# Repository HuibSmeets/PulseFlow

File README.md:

# PulseFlow
Control the speed of a cooling fan with your heart rate while riding/using your indoor trainer.

Image: Prototype, work in progress

## Description

**PulseFlow** is a small Arduino sketch that connects via BLE to a HR fitness sensor like those from Garmin, Wahoo and others. The fan is connected to a PWM controllable AC dimmer or a dimmer that exposes 2 pins: Output Zerocross detection, input triac trigger. These AC dimmers can be sourced from marketplaces like AliExpress.

## Warning
BE AWARE THAT YOU'LL BE WORKING WITH DEADLY LIVE VOLTAGES. TAKE APPROPRIATE SAFETY MEASURES WHEN CONNECTING PARTS AND WHILE USING THE DEVICE YOU CREATED. 

## Limitations

+ Your HR sensor must allow for multiple BLE connections as your trainer software/device will possiby have to connect to the sensor too using BLE (Garmin HR-Dual sensor supports multiple BLE connections)
+ Sensor pairing is hardcoded, see the sourcecode
+ Use a fan that has no electronic speed control of it's own.
+ The HR to fan speed mapping is hardcoded, see the sourcecode
+ In case of a PWM controlled dimmer:
  + The PWM signal is available on pin D6 (Arduino numbering)
  + Code to generate the PWM is Nano 33 BLE specific
+ In case of zero-cross/triac trigger dimmer:
  + Pin 2 (Arduino numbering) is used to detect the zero-crossing (interupt)
  + The triac trigger pulse is available on pin D6 (Arduino numbering)
  + The delay implementation between the zero-crossing and the triactrigger is Nano 33 BLE specific
+ As the NANO is a 3.3V device the AC dimmer you use must be 3.3v tolerable/compatible (or add levelshifting)
+ Installing the various parts in a metal of shielded housing can influense the BLE RF signal

## Possible enhancements

+ Do away with hardcoded pairing
+ Create an UI (e.g. a 2-Line display and rotary encoder) for pairing, map settings. 
+ Alternate fan speed mapping methods (speed, power,...).

## Change Log

### in development (main)
+ code cleanup
+ added battery level check
+ delayed switch off

### v1.1.0
+ added code for 2nd type of dimmer

### v1.0.0
+ Initial release

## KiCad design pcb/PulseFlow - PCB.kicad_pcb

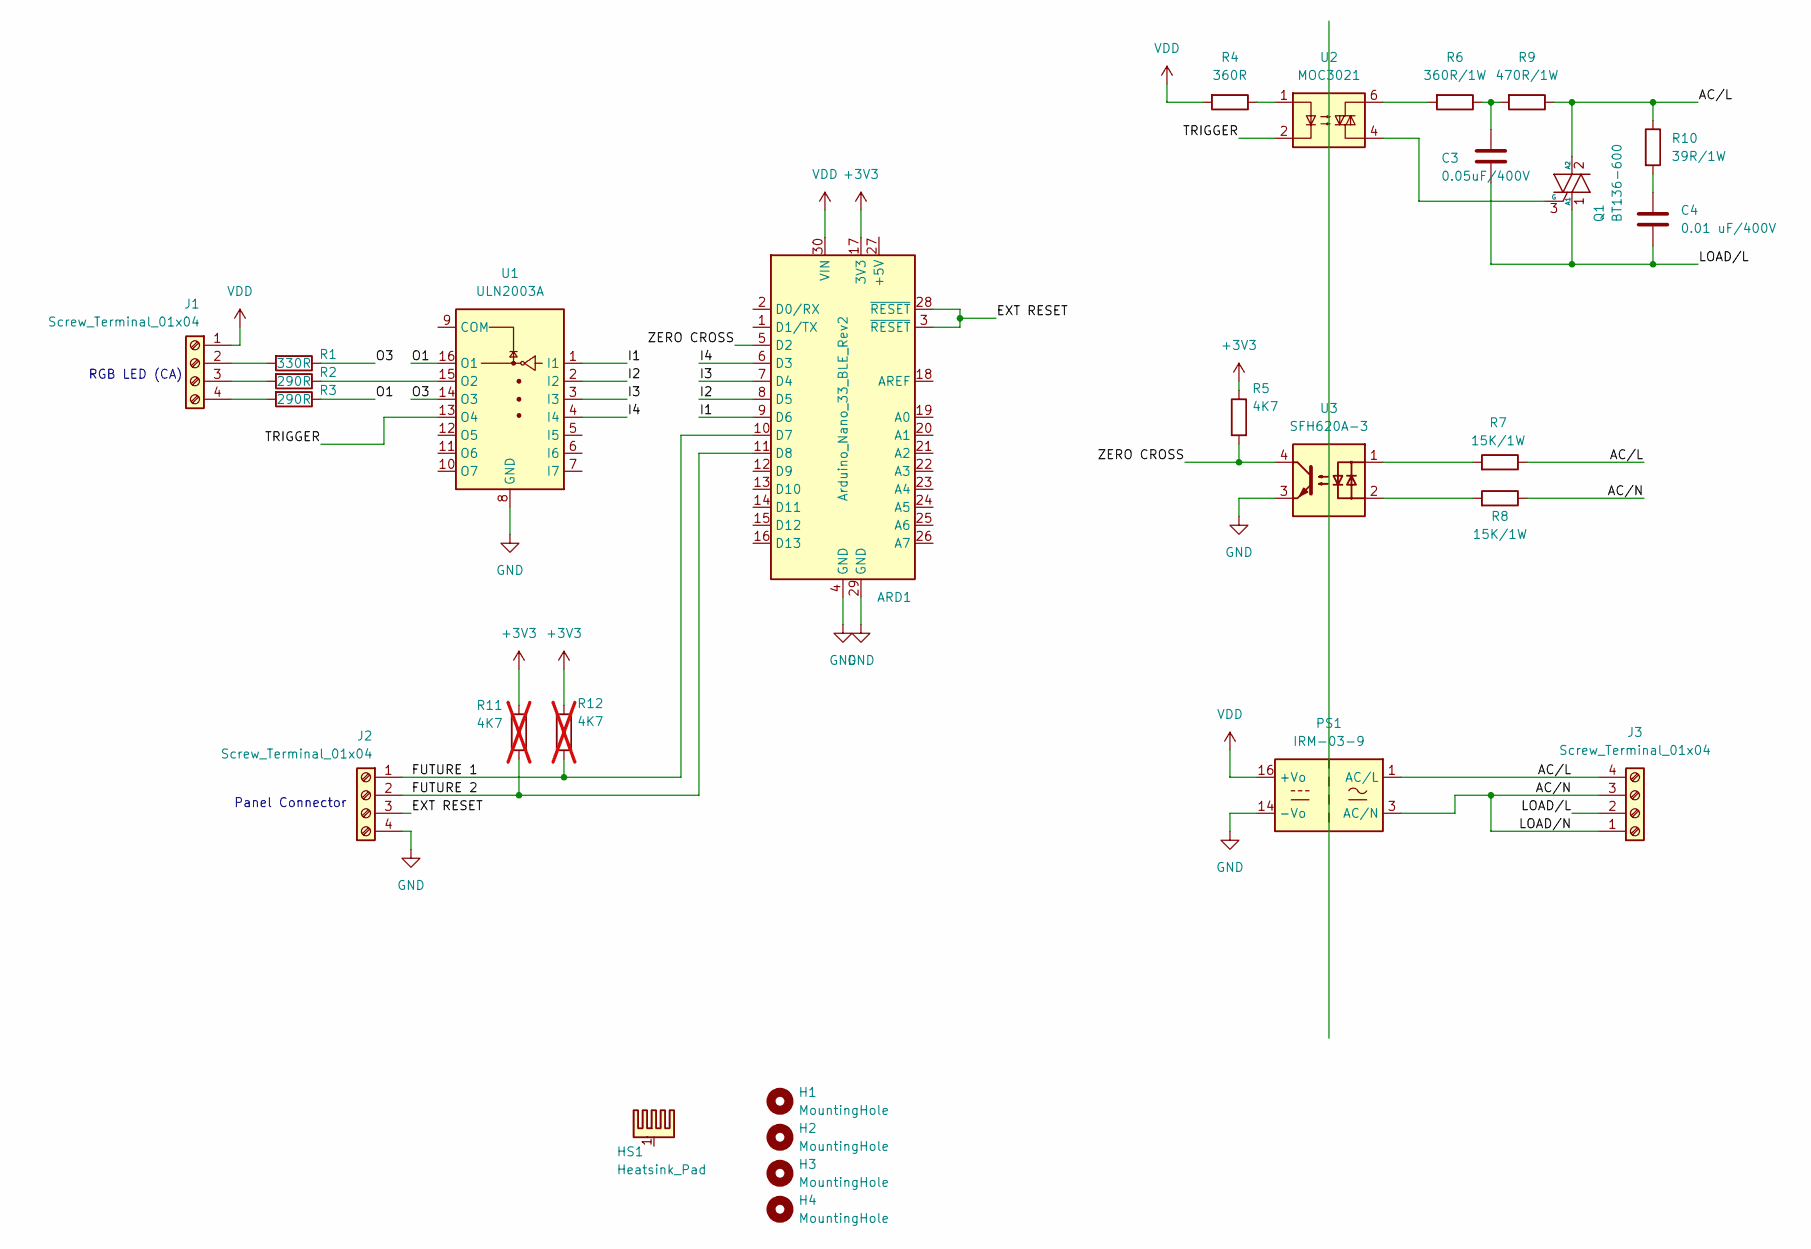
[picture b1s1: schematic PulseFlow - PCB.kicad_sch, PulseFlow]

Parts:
ARD1: Arduino_Nano_33_BLE_Rev2; Arduino_Nano_WithMountingHoles
C3: 0.05uF/400V; C_Rect_L13.0mm_W6.0mm_P10.00mm_FKS3_FKP3_MKS4
C4: 0.01 uF/400V; C_Rect_L10.0mm_W4.0mm_P7.50mm_FKS3_FKP3
H1, H2, H3, H4: MountingHole; MountingHole_3.2mm_M3_ISO14580
HS1: Heatsink_Pad; Heatsink_Fischer_SK-431-1x25mm
J1, J2: Screw_Terminal_01x04; TerminalBlock_Phoenix_MPT-0,5-4-2.54_1x04_P2.54mm_Horizontal
J3: Screw_Terminal_01x04; TerminalBlock_Phoenix_MKDS-1,5-4-5.08_1x04_P5.08mm_Horizont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
PS1: IRM-03-9; Converter_ACDC_MeanWell_IRM-03-xx_THT
Q1: BT136-600; TO-220-3_Vertical
R1: 330R; R_Axial_DIN0207_L6.3mm_D2.5mm_P10.16mm_Horizontal
R2, R3: 290R; R_Axial_DIN0207_L6.3mm_D2.5mm_P10.16mm_Horizontal
R4: 360R; R_Axial_DIN0207_L6.3mm_D2.5mm_P10.16mm_Horizontal
R5: 4K7; R_Axial_DIN0207_L6.3mm_D2.5mm_P10.16mm_Horizontal
R6: 360R/1W; R_Axial_DIN0207_L6.3mm_D2.5mm_P10.16mm_Horizontal
R7, R8: 15K/1W; R_Axial_DIN0207_L6.3mm_D2.5mm_P10.16mm_Horizontal
R9: 470R/1W; R_Axial_DIN0207_L6.3mm_D2.5mm_P10.16mm_Horizontal
R10: 39R/1W; R_Axial_DIN0207_L6.3mm_D2.5mm_P10.16mm_Horizontal
R11, R12: 4K7; R_Axial_DIN0207_L6.3mm_D2.5mm_P10.16mm_Horizontal; not fitted
U1: ULN2003A; DIP-16_W7.62mm
U2: MOC3021; DIP-6_W7.62mm
U3: SFH620A-3; DIP-4_W7.62mm

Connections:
+3V3: ARD1.17 (3V3), R5.1, R11.1, R12.1
/AC/L: J3.4, PS1.1 (AC/L), Q1.2 (A2), R7.1, R9.1, R10.1
/AC/N: J3.1, J3.3, PS1.3 (AC/N), R8.1
/EXT RESET: ARD1.3 (~RESET), ARD1.28 (~RESET), J2.3
/FUTURE 1: ARD1.10 (D7), J2.1, R12.2
/FUTURE 2: ARD1.11 (D8), J2.2, R11.2
/I1: ARD1.9 (D6), U1.1 (I1)
/I2: ARD1.8 (D5), U1.2 (I2)
/I3: ARD1.7 (D4), U1.3 (I3)
/I4: ARD1.6 (D3), U1.4 (I4)
/LOAD/L: C3.2, C4.2, J3.2, Q1.1 (A1)
/O1: R3.1, U1.16 (O1)
/O3: R1.1, U1.14 (O3)
/TRIGGER: U1.13 (O4), U2.2
/ZERO CROSS: ARD1.5 (D2), R5.2, U3.4
GND: ARD1.4 (GND), ARD1.29 (GND), J2.4, PS1.14 (-Vo), U1.8 (GND), U3.3
unnamed: C3.1, R6.1, R9.2
unnamed: C4.1, R10.2
unnamed: J1.2, R1.2
unnamed: J1.3, R2.2
unnamed: J1.4, R3.2
unnamed: Q1.3 (G), U2.4
unnamed: R4.1, U2.1
unnamed: R6.2, U2.6
unnamed: R7.2, U3.1
unnamed: R8.2, U3.2
unnamed: R2.1, U1.15 (O2)
VDD: ARD1.30 (VIN), J1.1, PS1.16 (+Vo), R4.2

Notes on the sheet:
Panel Connector
RGB LED (CA)

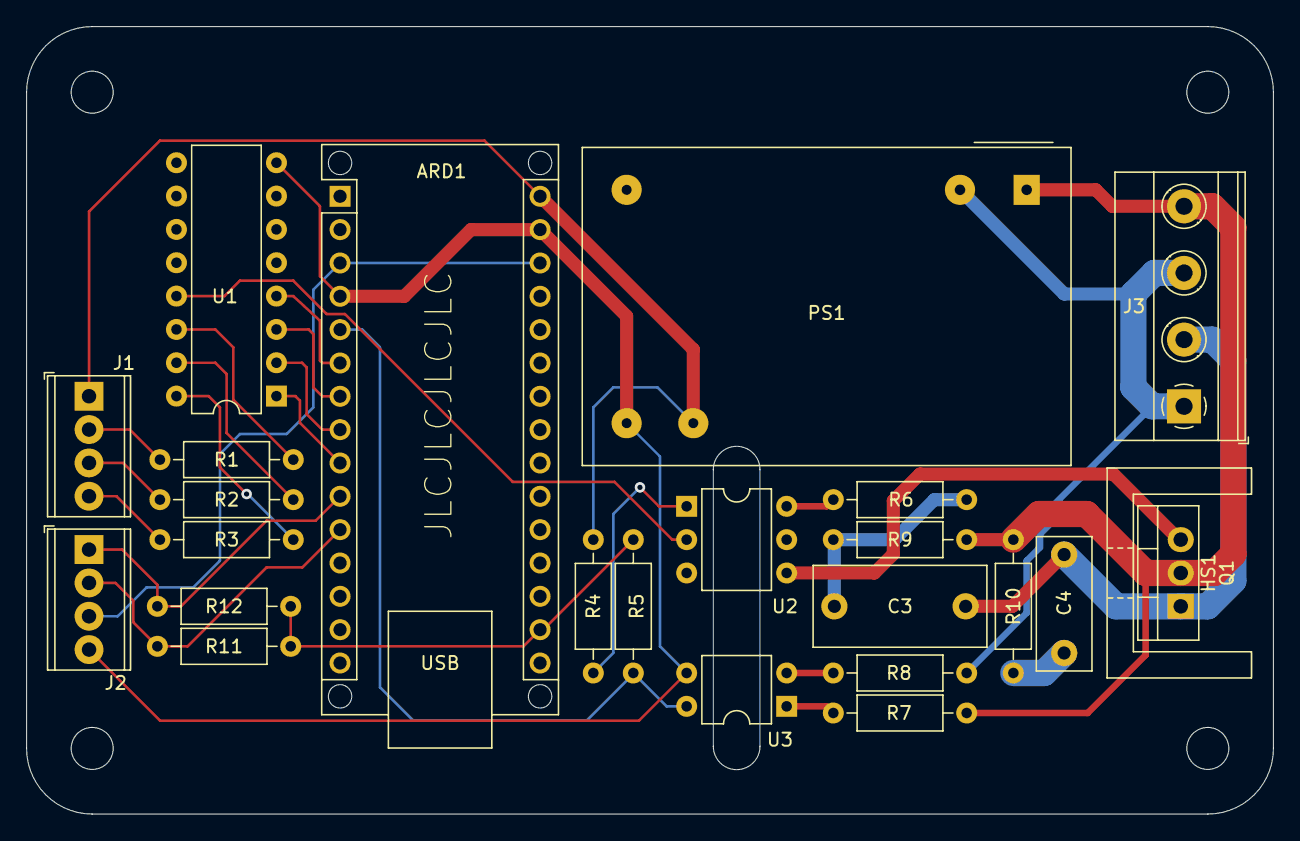
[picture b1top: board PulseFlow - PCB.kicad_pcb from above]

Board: 2 copper layers, 95.0 x 60.0 mm, 28 parts (0 on the bottom side), 28 nets.

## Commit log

2024-11-21 Initial upload
2024-11-21 Added remark about type of fan to be used.
2024-11-21 Small corrections
2024-11-21 Small corrections (again)
2024-11-21 Various corrections in the comments
2024-11-22 Added a photo
2024-11-22 Further clarification
2024-11-22 Rename IMG_3430.JPG to Prototype.JPG
2024-11-22 Update README.md (#1)
2024-11-22 Revert "Update README.md (#1)"
    This reverts commit 7f83956087c372674b5bedd7a21e3b56704f424e.
2024-11-25 Possible enhancement added: Battery check
2024-11-26 Alternative Dimmer
    Code added to use a different dimmer that only exposes 2 pins: one to detect the sinus zero-crossing and a pin to trigger the triac.
2024-11-26 Variables names update
2024-11-30 Reset BLE tweak
    BLE.start() failed the other day in the reset every 5 minutes while scanning loop, changed to code to retry indefinitely.
2024-12-01 Changed BLE restart to a system reboot
2024-12-01 Some code cleanup + battery level check added
2024-12-03 Code cleanup
2024-12-08 Delete PulseFlow.ino
    Moved
2024-12-08 Bug fix
2024-12-08 Fix the bug fix
